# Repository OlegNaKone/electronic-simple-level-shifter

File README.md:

# electronic-simple-level-shifter

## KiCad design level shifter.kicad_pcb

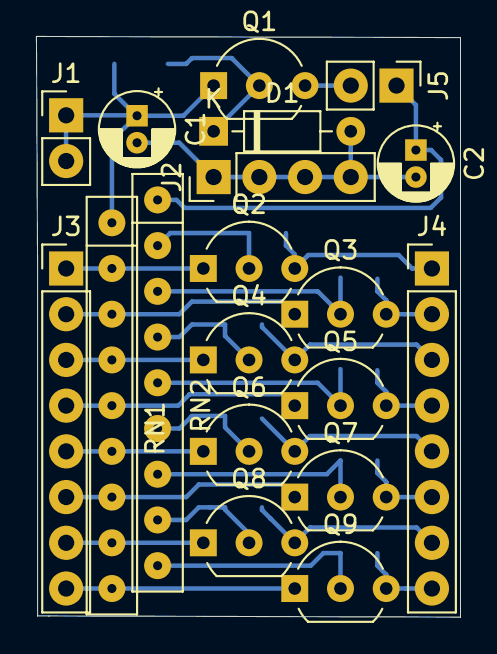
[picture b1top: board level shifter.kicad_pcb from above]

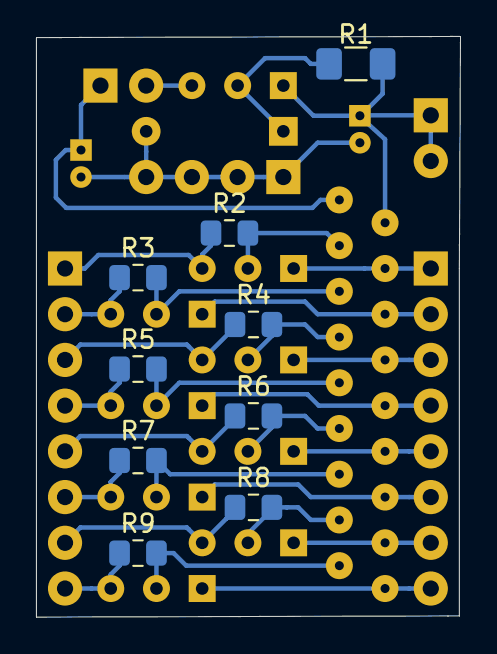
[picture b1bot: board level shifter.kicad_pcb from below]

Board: 2 copper layers, 23.6 x 32.3 mm, 28 parts (9 on the bottom side), 29 nets.

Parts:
C1, C2: 10u; CP_Radial_D4.0mm_P1.50mm
D1: 4V; D_DO-35_SOD27_P7.62mm_Horizontal
J1, J5: Conn_01x02; PinHeader_1x02_P2.54mm_Vertical
J2: Conn_01x04; PinHeader_1x04_P2.54mm_Vertical
J3: 5v level; PinHeader_1x08_P2.54mm_Vertical
J4: 3v3 level; PinHeader_1x08_P2.54mm_Vertical
Q1, Q2, Q3, Q4, Q5, Q6, Q7, Q8, Q9: BC547; TO-92_Inline_Wide
R1: 1k; R_1206_3216Metric_Pad1.42x1.75mm_HandSolder
R2, R3, R4, R5, R6, R7, R8, R9: 1k; R_0805_2012Metric_Pad1.15x1.40mm_HandSolder
RN1: 8 x 10k; R_Array_SIP9
RN2: 8 x 1k; R_Array_SIP9

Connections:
+3V3: C2.1, J5.1, RN2.1
+5V: C1.1, J1.1, J1.2, Q1.1, R1.2, RN1.1
/3v_0: J4.1, Q2.3, R2.1
/3v_1: J4.2, Q3.3, R3.1
/3v_2: J4.3, Q4.3, R4.1
/3v_3: J4.4, Q5.3, R5.1
/3v_4: J4.5, Q6.3, R6.1
/3v_5: J4.6, Q7.3, R7.1
/3v_6: J4.7, Q8.3, R8.1
/3v_7: J4.8, Q9.3, R9.1
/3v_pu0: Q2.2, R2.2, RN2.2
/3v_pu1: Q3.2, R3.2, RN2.3
/3v_pu2: Q4.2, R4.2, RN2.4
/3v_pu3: Q5.2, R5.2, RN2.5
/3v_pu4: Q6.2, R6.2, RN2.6
/3v_pu5: Q7.2, R7.2, RN2.7
/3v_pu6: Q8.2, R8.2, RN2.8
/3v_pu7: Q9.2, R9.2, RN2.9
/5v_0: J3.1, Q2.1, RN1.2
/5v_1: J3.2, Q3.1, RN1.3
/5v_2: J3.3, Q4.1, RN1.4
/5v_3: J3.4, Q5.1, RN1.5
/5v_4: J3.5, Q6.1, RN1.6
/5v_5: J3.6, Q7.1, RN1.7
/5v_6: J3.7, Q8.1, RN1.8
/5v_7: J3.8, Q9.1, RN1.9
GND: C1.2, C2.2, D1.2, J2.1, J2.2, J2.3, J2.4
unnamed: D1.1, Q1.2, R1.1
unnamed: J5.2, Q1.3

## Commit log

2022-04-06 init
